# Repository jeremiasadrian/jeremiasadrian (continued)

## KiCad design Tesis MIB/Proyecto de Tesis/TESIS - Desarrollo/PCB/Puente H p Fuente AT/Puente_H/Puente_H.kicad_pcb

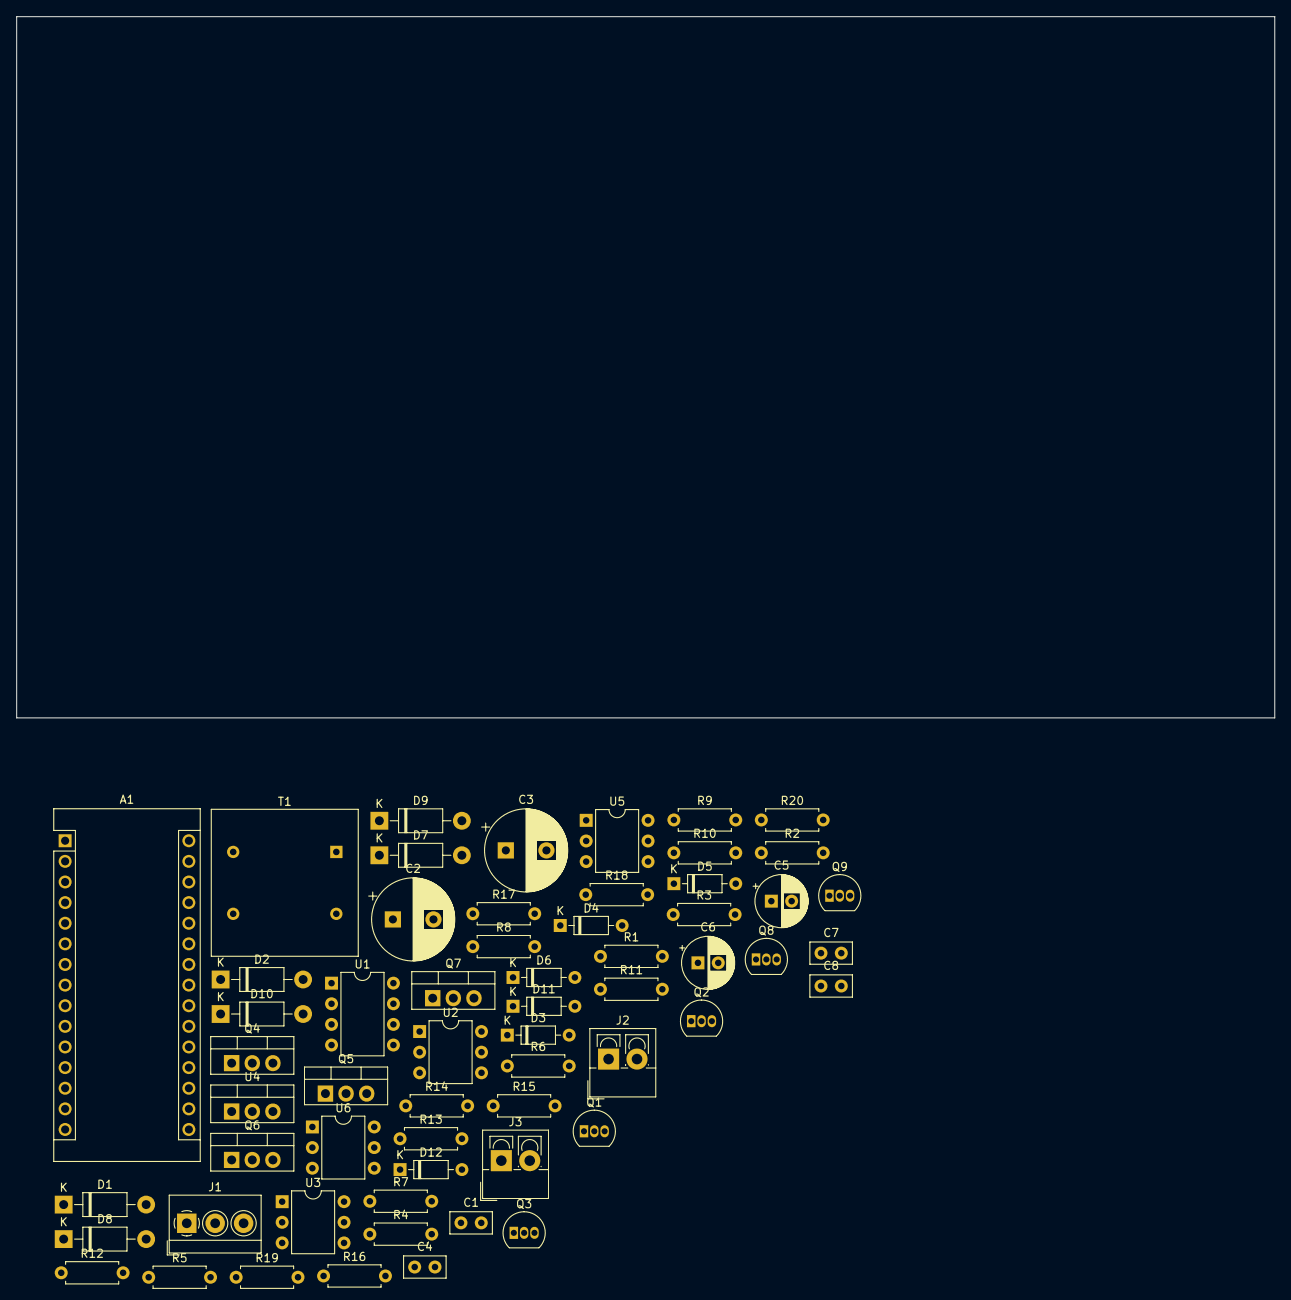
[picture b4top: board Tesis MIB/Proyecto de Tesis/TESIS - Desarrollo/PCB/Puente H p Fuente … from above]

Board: 2 copper layers, 154.9 x 86.4 mm, 60 parts (0 on the bottom side), 39 nets, no tracks yet.

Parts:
A1: Arduino_Nano_v3.x; Arduino_Nano
C1: 10nF; C_Disc_D5.0mm_W2.5mm_P2.50mm
C2, C3: 100uF; CP_Radial_D10.0mm_P5.00mm
C4, C8: 100nF; C_Disc_D5.0mm_W2.5mm_P2.50mm
C5: 10uF; CP_Radial_D6.3mm_P2.50mm
C6: 100uF; CP_Radial_D6.3mm_P2.50mm
C7: 330nF; C_Disc_D5.0mm_W2.5mm_P2.50mm
D1, D2, D7, D8, D9, D10: 1N4007; D_DO-41_SOD81_P10.16mm_Horizontal
D3, D4: 1N4148; D_DO-35_SOD27_P7.62mm_Horizontal
D5, D6, D11, D12: 1N53xxB; D_DO-35_SOD27_P7.62mm_Horizontal
J1: Screw_Terminal_01x03; TerminalBlock_4Ucon_1x03_P3.50mm_Horizontal
J2, J3: Screw_Terminal_01x02; TerminalBlock_4Ucon_1x02_P3.50mm_Vertical
Q1, Q2, Q8, Q9: BC547; TO-92_Inline
Q3: BC337; TO-92_Inline
Q4, Q5, Q6, Q7: IRF3205; TO-220-3_Vertical
R1: 2.2k; R_Axial_DIN0207_L6.3mm_D2.5mm_P7.62mm_Horizontal
R2, R3, R6, R7, R9, R10, R11, R12, R13, R14, R15, R16, R17, R18, R19, R20: R; R_Axial_DIN0207_L6.3mm_D2.5mm_P7.62mm_Horizontal
R4: 6.8k; R_Axial_DIN0207_L6.3mm_D2.5mm_P7.62mm_Horizontal
R5: 4.7k; R_Axial_DIN0207_L6.3mm_D2.5mm_P7.62mm_Horizontal
R8: 330; R_Axial_DIN0207_L6.3mm_D2.5mm_P7.62mm_Horizontal
T1: Transformer_1P_1S; Transformer_NF_ETAL_1-1_P1200
U1: NA555P; DIP-8_W7.62mm
U2, U3, U5, U6: 4N27; DIP-6_W7.62mm
U4: LM7805_TO220; TO-220-3_Vertical

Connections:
+5V: A1.27 (+5V), U2.1, U3.1, U5.1, U6.1
+12V: C7.1, D3.2 (A), D7.1 (K), D9.1 (K), J2.1, Q4.2 (D), Q6.2 (D), R1.2, R8.1, R9.2, R16.2, U1.4 (R), U1.8 (VCC), U4.1 (VI)
/+5v: C8.1, J3.1, U4.3 (VO)
/+24v: C6.1, D4.1 (K), R10.2, R15.2
/+300v: C2.1, D1.1 (K), J1.1
/-300v: C3.2, D2.2 (A), J1.3
/Puente_A: A1.5 (D2), R3.1, R20.2
/Puente_B: A1.6 (D3), R2.1, R19.2
/SECout: D1.2 (A), D2.1 (K), T1.4 (SB)
GND: A1.4 (GND), A1.29 (GND), C1.2, C2.2, C3.1, C4.2, C6.2, C7.2, C8.2, D5.2 (A), D8.2 (A), D10.2 (A), D12.2 (A), J1.2, J2.2, J3.2, Q1.3 (E), Q2.3 (E), Q3.3 (E), Q5.3 (S), Q7.3 (S), Q8.3 (E), Q9.3 (E), R11.2, R14.1, T1.3 (SA), U1.1 (GND), U4.2 (GND)
unnamed: C1.1, U1.5 (CV)
unnamed: C4.1, R4.1, U1.2 (TR), U1.6 (THR)
unnamed: C5.1, D3.1 (K), D4.2 (A)
unnamed: C5.2, Q3.1 (C), R8.2
unnamed: D5.1 (K), Q5.1 (G), R11.1, U3.4
unnamed: D6.1 (K), Q4.1 (G), R12.1, U2.4
unnamed: D6.2 (A), D7.2 (A), D8.1 (K), Q4.3 (S), Q5.2 (D), R12.2
unnamed: D9.2 (A), D10.1 (K), D11.2 (A), Q6.3 (S), Q7.2 (D), R13.1, T1.1 (AA)
unnamed: D11.1 (K), Q6.1 (G), R13.2, U6.4
unnamed: D12.1 (K), Q7.1 (G), R14.2, U5.4
unnamed: Q1.1 (C), R6.2
unnamed: Q1.2 (B), R2.2
unnamed: Q2.1 (C), R7.2
unnamed: Q2.2 (B), R3.2
unnamed: Q3.2 (B), R5.1
unnamed: Q8.1 (C), R17.1
unnamed: Q8.2 (B), R19.1
unnamed: Q9.1 (C), R18.1
unnamed: Q9.2 (B), R20.1
unnamed: R1.1, R4.2, U1.7 (DIS)
unnamed: R5.2, U1.3 (Q)
unnamed: R6.1, U2.2
unnamed: R7.1, U3.2
unnamed: R9.1, U3.5
unnamed: R10.1, U2.5
unnamed: R15.1, U6.5
unnamed: R16.1, U5.5
unnamed: R17.2, U5.2
unnamed: R18.2, U6.2

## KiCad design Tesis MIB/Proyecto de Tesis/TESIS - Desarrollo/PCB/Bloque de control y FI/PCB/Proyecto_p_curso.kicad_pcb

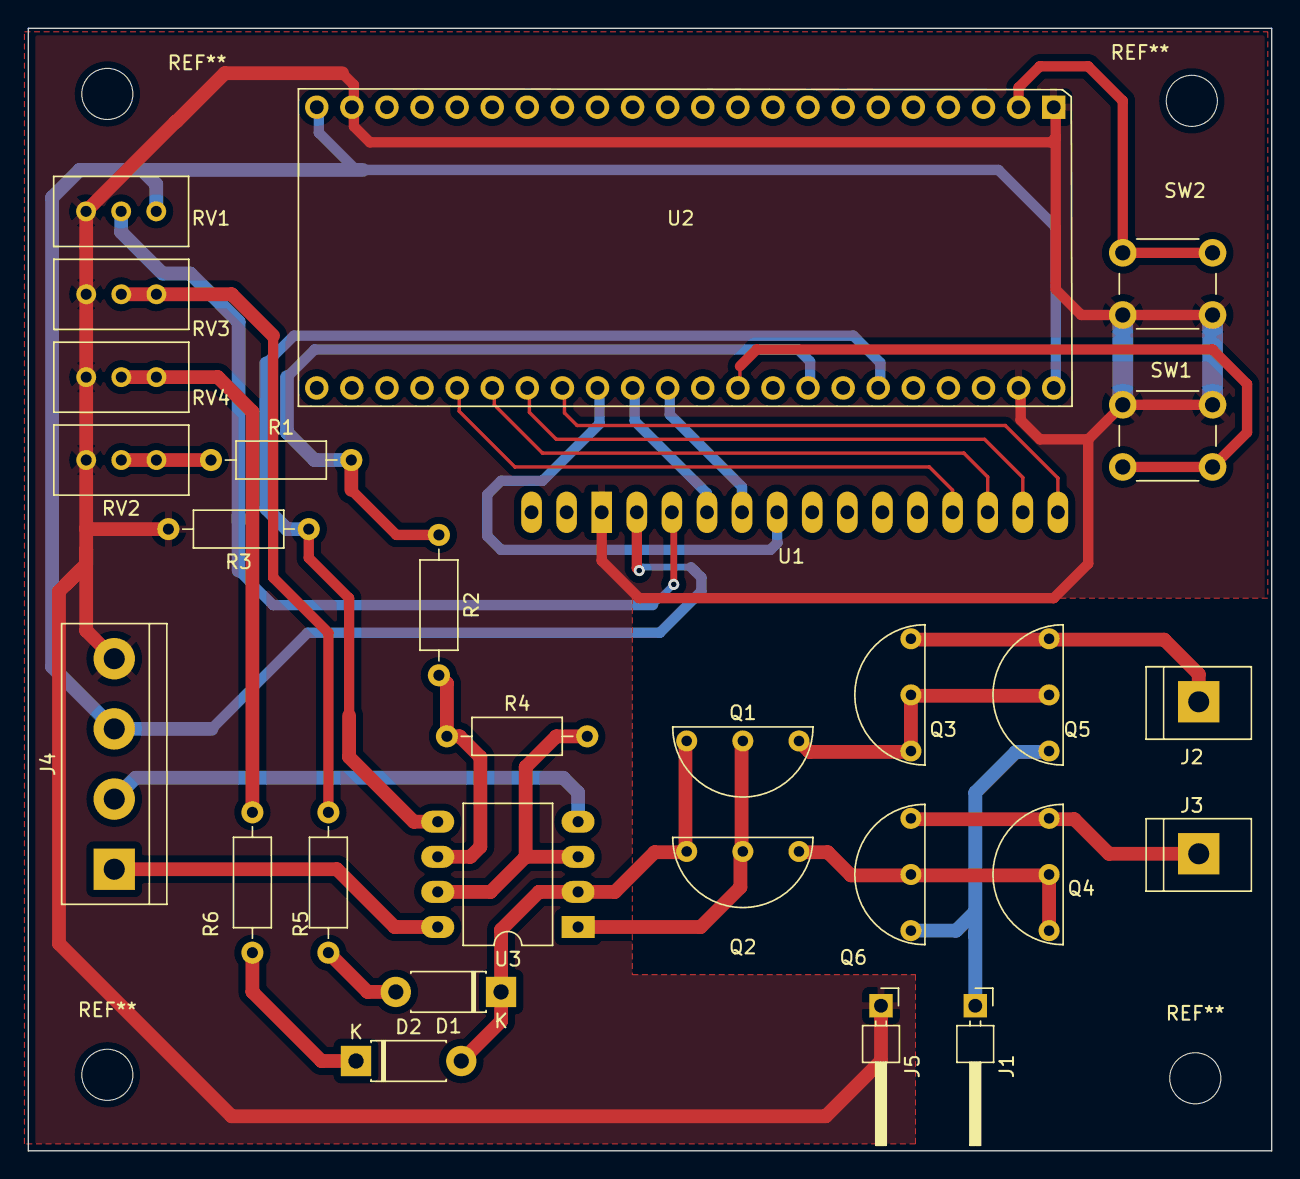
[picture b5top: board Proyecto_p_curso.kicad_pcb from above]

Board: 2 copper layers, 90.0 x 81.2 mm, 28 parts (0 on the bottom side), 30 nets.

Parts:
D1, D2: 1N4148; D_DO-41_SOD81_P7.62mm_Horizontal
J1, J5: Conn_01x01_Male; PinHeader_1x01_P2.54mm_Horizontal
J2, J3: Screw_Terminal_01x01; TerminalBLock_bornier-1_P5.08mm
J4: Screw_Terminal_01x04; TerminalBlock_bornier-4_P5.08mm
Q1, Q4, Q6: BF422; BF42X
Q2: BG421; BF42X
Q3, Q5: BF421; BF42X
R1, R5: 10k; R_Axial_DIN0207_L6.3mm_D2.5mm_P10.16mm_Horizontal
R2: 22k; R_Axial_DIN0207_L6.3mm_D2.5mm_P10.16mm_Horizontal
R3: 6k8; R_Axial_DIN0207_L6.3mm_D2.5mm_P10.16mm_Horizontal
R4: 47k; R_Axial_DIN0207_L6.3mm_D2.5mm_P10.16mm_Horizontal
R6: 3k3; R_Axial_DIN0207_L6.3mm_D2.5mm_P10.16mm_Horizontal
RV1, RV4: 5k; Potentiometer_Bourns_3296W_Vertical
RV2: 2k; Potentiometer_Bourns_3296W_Vertical
RV3: 10k; Potentiometer_Bourns_3296W_Vertical
SW1, SW2: SW_Push; SW_PUSH_6mm_H7.3mm
U1: LCD-016N002L; LCD_pinsonly
U2: PSoC4_kit049_(CY8C4245AXI-483); PinSocket_2x22_P2.54mm_Vertical_2
U3: TL082; DIP-8_W10.16mm_LongPads

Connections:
+5V: J4.3, RV1.1, U1.2 (VDD), U2.22 (VDD), U2.23 (VDD)
+12V: J4.1, U3.8 (V+)
-12V: J4.2, U3.4 (V-)
/Control_y_salida/But_Dec: SW1.2, U2.32 (P1.0)
/Control_y_salida/But_Inc: SW2.2, U2.2 (P2.0)
/Control_y_salida/IDAC_Neg: R1.2, R2.1, U2.30 (P1.2)
/Control_y_salida/IDAC_Pos: R3.1, U2.28 (P1.4), U3.5 (+)
/Control_y_salida/Iout: J1.1, Q5.1 (C), Q6.1 (C)
/Control_y_salida/LCD_D4: U1.11 (DB4), U2.40 (P0.0)
/Control_y_salida/LCD_D5: U1.12 (DB5), U2.39 (P0.1)
/Control_y_salida/LCD_D6: U1.13 (DB6), U2.38 (P0.2)
/Control_y_salida/LCD_D7: U1.14 (DB7), U2.37 (P0.3)
/Control_y_salida/LCD_E: U1.6 (E), U2.36 (P0.4)
/Control_y_salida/LCD_RS: U1.4 (RS), U2.35 (P0.5)
/Control_y_salida/LCD_R/W: U1.5 (R/~W), U2.34 (P0.6)
GND: J4.4, J5.1, R3.2, RV1.3, RV2.3, RV3.3, RV4.3, SW1.1, SW2.1, U1.1 (VSS), U2.1 (GND), U2.21 (GND), U2.24 (GND)
unnamed: D1.1 (K), D2.2 (A), Q1.3 (E), Q2.3 (E), U3.2 (-)
unnamed: D1.2 (A), R5.2
unnamed: D2.1 (K), R6.2
unnamed: Q1.1 (C), Q3.1 (C), Q3.2 (B), Q5.2 (B)
unnamed: Q1.2 (B), Q2.2 (B), U3.1
unnamed: Q2.1 (C), Q4.1 (C), Q4.2 (B), Q6.2 (B)
unnamed: R1.1, RV2.1, RV2.2
unnamed: R2.2, R4.1, U3.6 (-)
unnamed: R4.2, U3.3 (+), U3.7
unnamed: R5.1, RV3.1, RV3.2
unnamed: R6.1, RV4.1, RV4.2
unnamed: RV1.2, U1.3 (VO)
VCC: J2.1, Q3.3 (E), Q5.3 (E)
VEE: J3.1, Q4.3 (E), Q6.3 (E)

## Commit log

2023-05-30 Información de Tesis MIB
2023-05-31 avance_en_PCB_fuente
2023-06-04 actualiza info de Tesis
    Incorpora archivos de simulación de propuesta de fuente en Proteus y los archivos de Kicad del mismo circuito.
2023-06-04 Agrega archivos del PCB del Bloque de control
2023-06-04 modificaciones del PCB
2024-03-22 actualiza a 22-3-2024
2024-03-25 Agrega Paper sobre mecanorreceptores
2024-03-25 agrega planilla de relevamiento del elestroestimulador
2024-06-15 Actualiza avances
    Se incorporan varios artículos de referencia y se actualiza el documento de Tesis con el Cap 1 (pag. 19 a 39).
2024-07-07 Actualiza avance del CAP 2
    Avances en el Capitulo 2 del Documento de Tesis: Figuras y sol queda pendiente los puntos de Desarrollo de Firmware y PCB para terminar la "1ra parte".
2024-07-13 Acualización del CAP2
    Finalización de la 1ra parte del CAP2, redacción de titulos y subtitulos para esquematizar los CAP3 y CAP4, actualización de los indices de Contenidos, Tablas y Figuras y Referencias insertadas (hast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
2024-07-22 Actualiza CAP 2 parcial 2
    Actualiza el documento de tesis con el CAP 2 casi finalizado, solo resto agregar "Simulaciones" y cierre final.
2024-07-26 Actualiza CAP 2 COMPLETO
    Documento de tesis MIB actualizado con la Capitulo 2 completo y con índices (contenidos, tablas y figuras) y referencias actualizadas hasta lo último.
2024-11-28 Actualiza Pruebas
    Agrega planilla, gráficos y capturas del osciloscopio para el CAP3
2024-11-28 Actualiza info para el CAP3
2024-12-27 CAP 3 finalizado e inicio del 4to
    Redactado la discución de resultados
2026-03-30 ultima
